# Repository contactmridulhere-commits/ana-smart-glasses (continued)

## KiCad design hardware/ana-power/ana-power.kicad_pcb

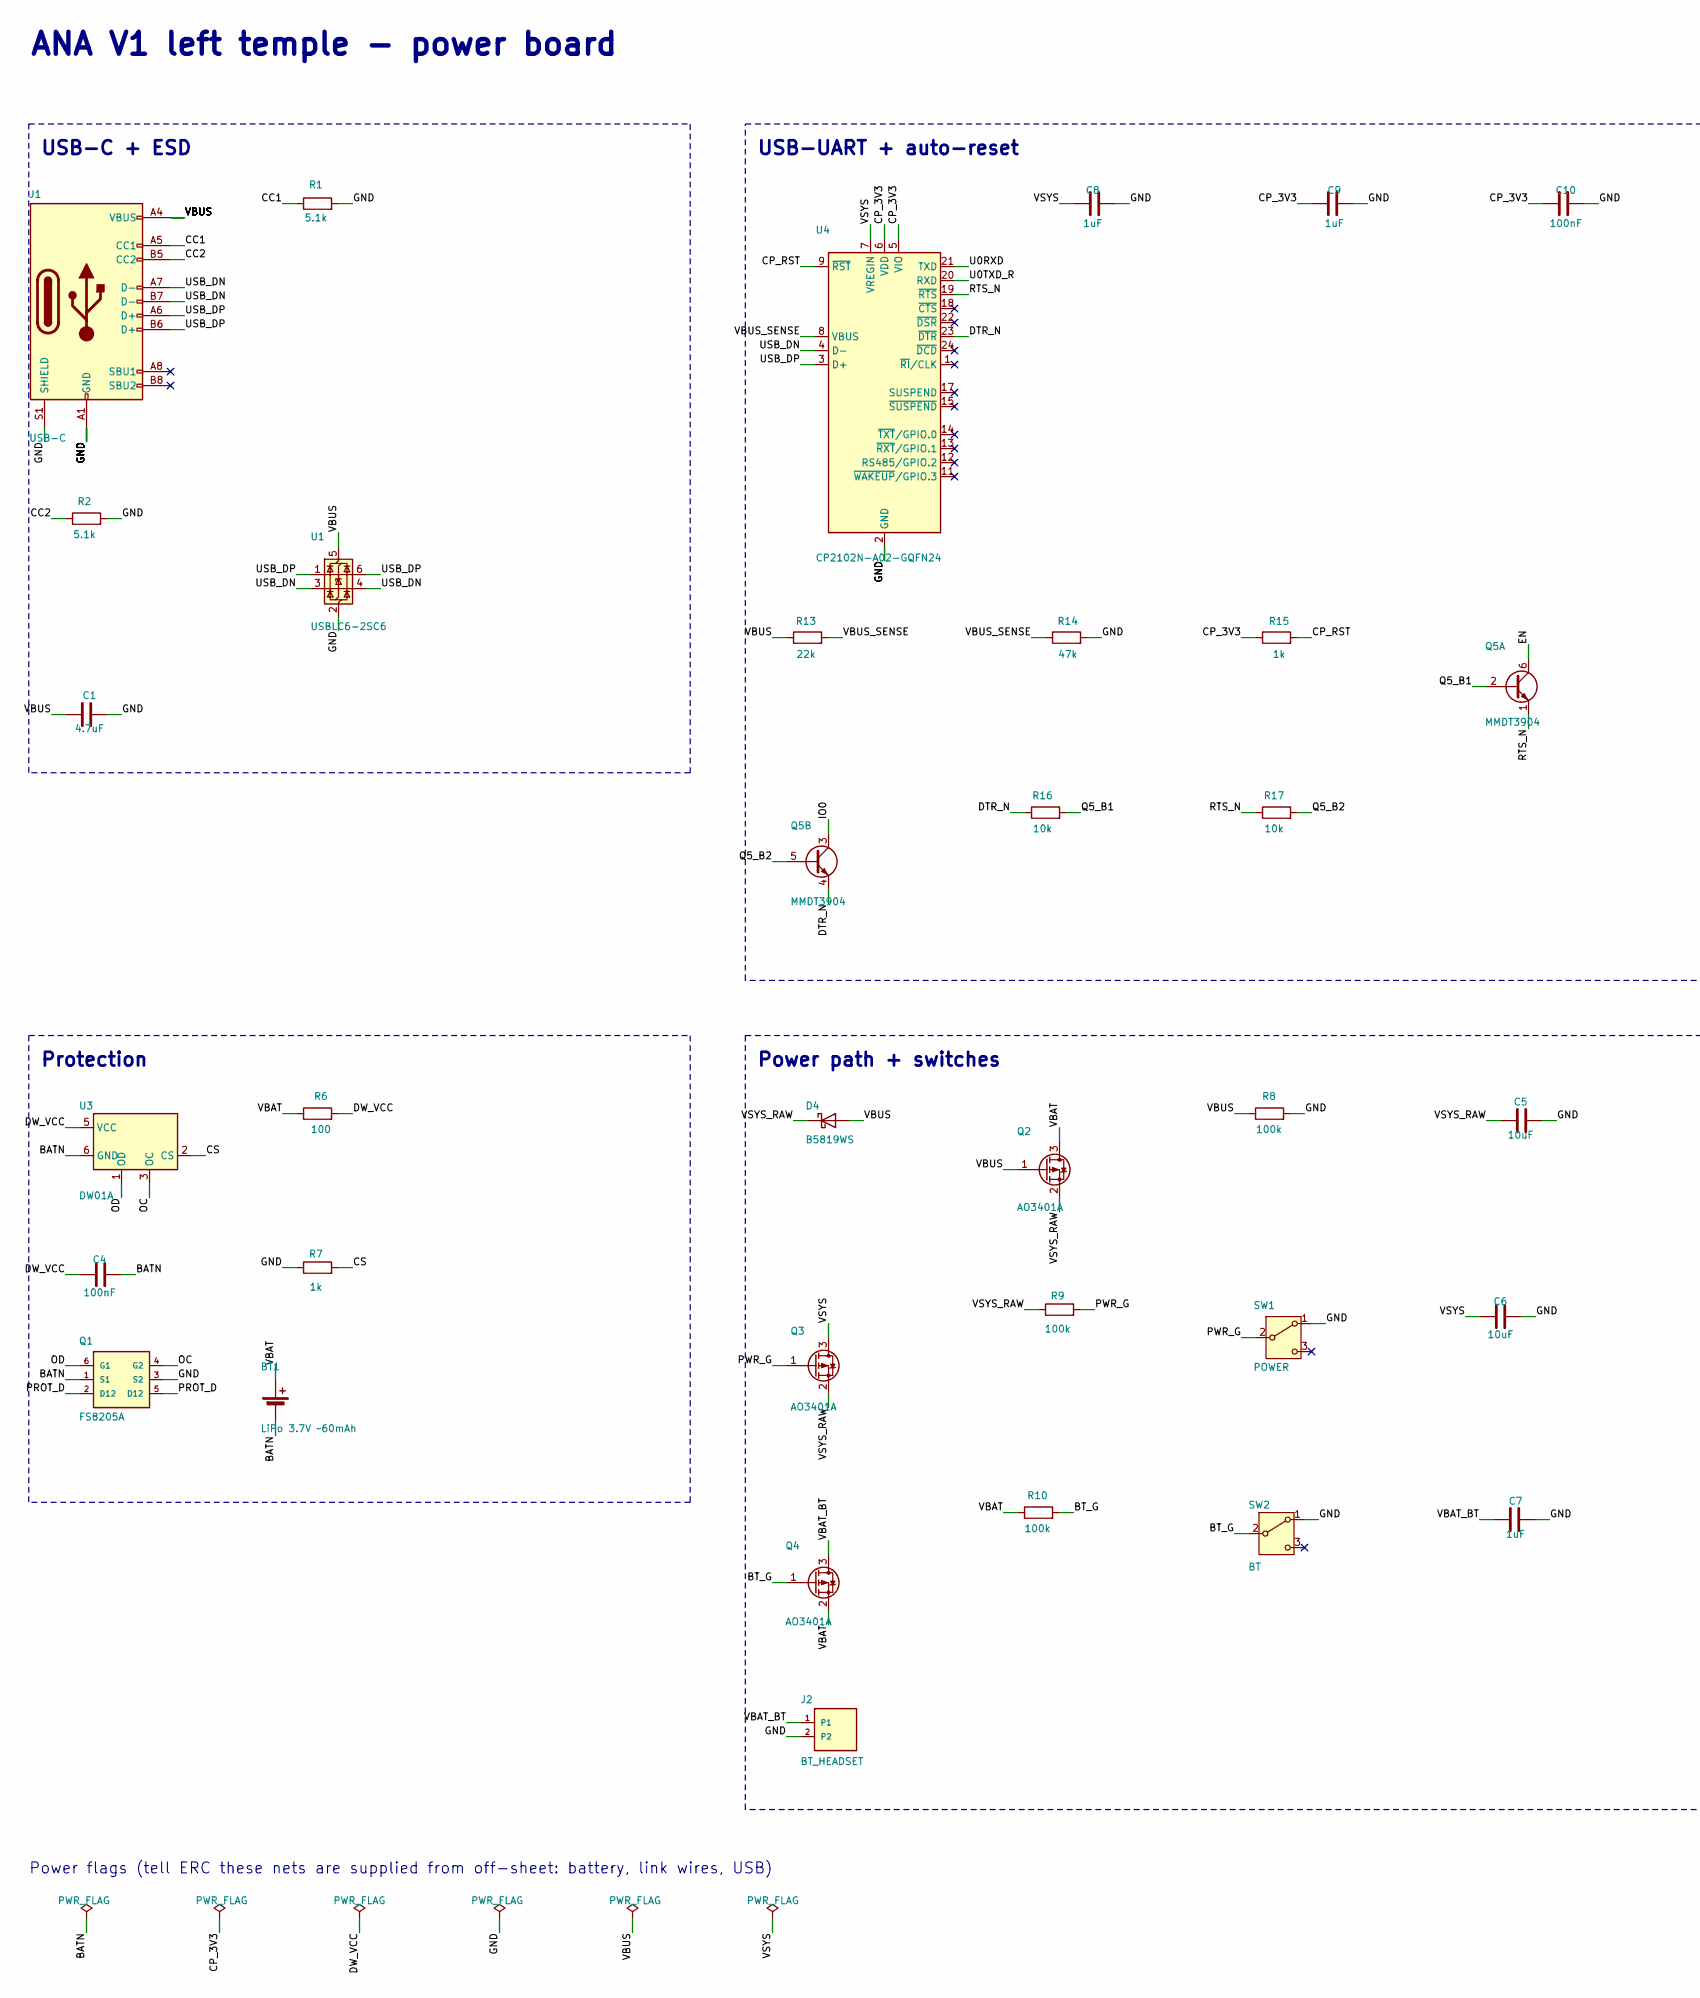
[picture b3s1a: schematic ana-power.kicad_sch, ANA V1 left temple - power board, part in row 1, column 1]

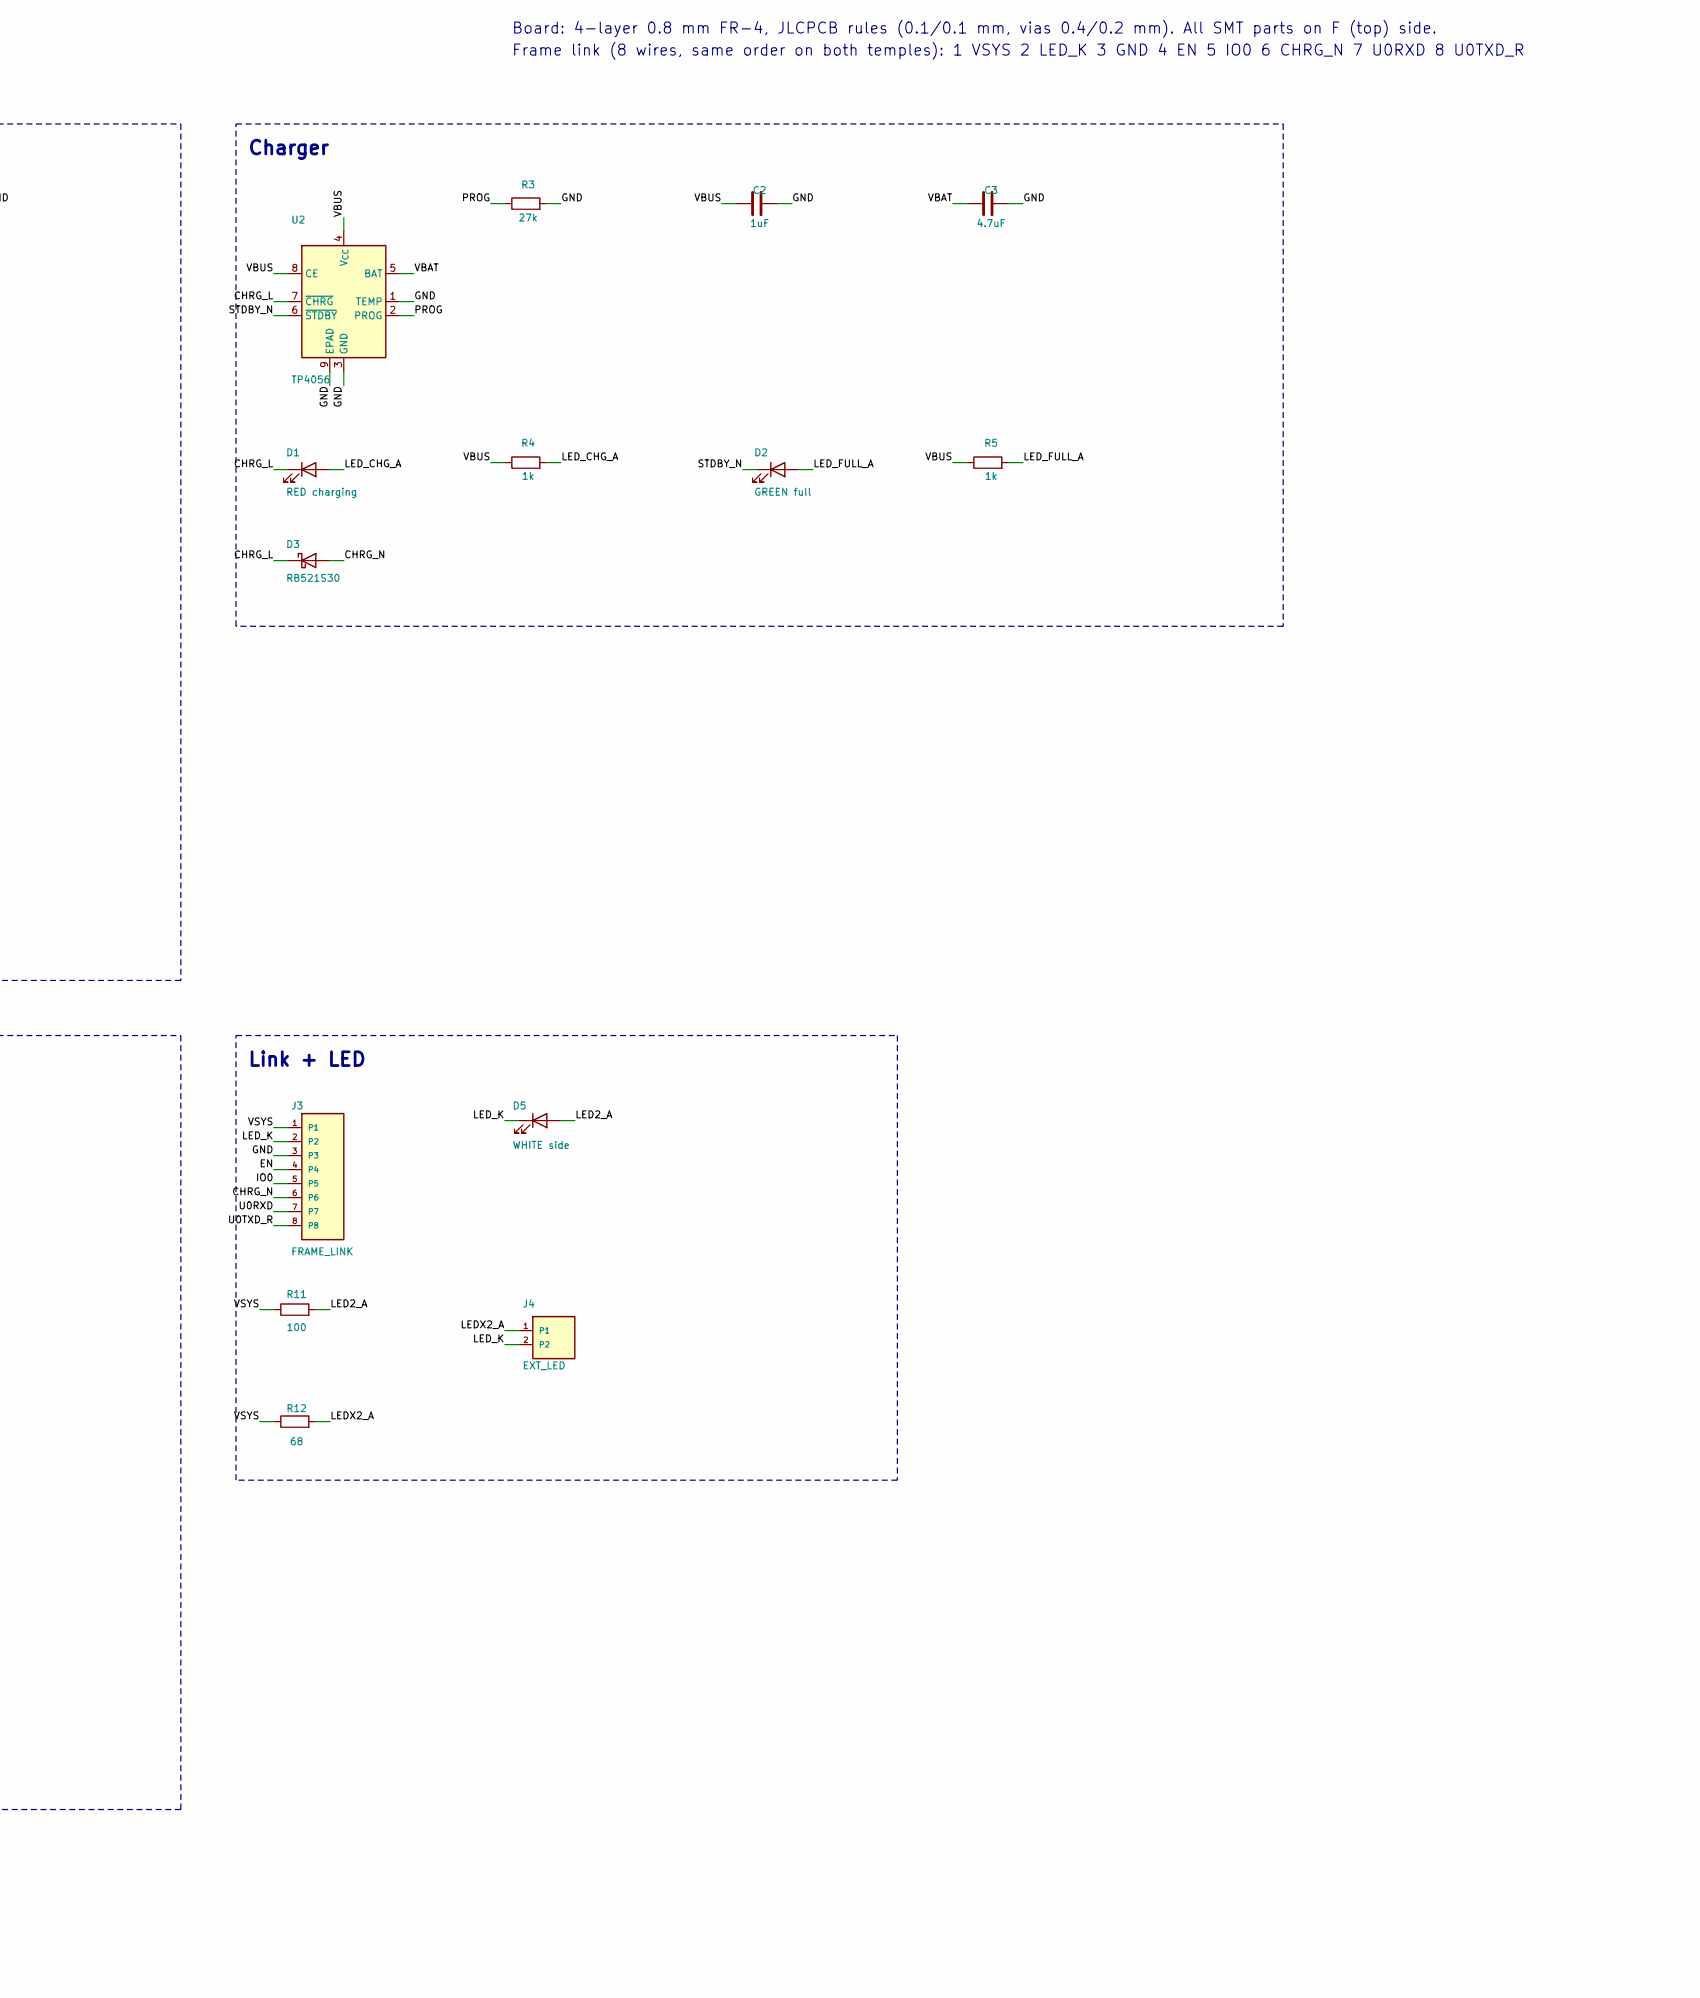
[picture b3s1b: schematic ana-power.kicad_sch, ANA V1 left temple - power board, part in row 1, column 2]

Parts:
BT1: LiPo 3.7V ~60mAh; BatteryPads_2x2.5mm
C1, C3: 4.7uF; C_0402_1005Metric; LCSC C469468
C2, C7, C8, C9: 1uF; C_0402_1005Metric; LCSC C52923
C4, C10: 100nF; C_0402_1005Metric; LCSC C1525
C5, C6: 10uF; C_0603_1608Metric; LCSC C380317
D1: RED charging; LED_0402_1005Metric; MPN NCD0402R1; LCSC C130719
D2: GREEN full; LED_0402_1005Metric; MPN NCD0402G1; LCSC C130723
D3: RB521S30; D_SOD-523; MPN RB521S30T1G; LCSC C145179
D4: B5819WS; D_SOD-323; MPN B5819WS; LCSC C64886
D5: WHITE side; LED_SideView_1.6x0.75mm_YLED0602; MPN YLED0602WSIDE; LCSC C46635136
J1: USB-C; USB_C_Receptacle_HRO_TYPE-C-31-M-12; MPN TYPE-C-31-M-12; LCSC C165948
J2: BT_HEADSET; WirePads_1x02_P1.50mm
J3: FRAME_LINK; WirePads_1x08_P1.50mm
J4: EXT_LED; WirePads_1x02_P1.50mm
Q1: FS8205A; SOT-23-6; MPN FS8205A; LCSC C908265
Q2, Q3, Q4: AO3401A; SOT-23; MPN AO3401A; LCSC C15127
Q5: MMDT3904; SOT-363_SC-70-6; MPN MMDT3904-7-F; LCSC C83572
R1, R2: 5.1k; R_0402_1005Metric; LCSC C25905
R3: 27k; R_0402_1005Metric; LCSC C25771
R4, R5, R7, R15: 1k; R_0402_1005Metric; LCSC C11702
R6, R11: 100; R_0402_1005Metric; LCSC C25076
R8, R9, R10: 100k; R_0402_1005Metric; LCSC C25741
R12: 68; R_0402_1005Metric; LCSC C25131
R13: 22k; R_0402_1005Metric; LCSC C25768
R14: 47k; R_0402_1005Metric; LCSC C25792
R16, R17: 10k; R_0402_1005Metric; LCSC C25744
SW1: POWER; SW_SPDT_Shouhan_MSK12C02; MPN MSK12C02; LCSC C431540
SW2: BT; SW_SPDT_Shouhan_MSK12C02; MPN MSK12C02; LCSC C431540
U1: USBLC6-2SC6; SOT-23-6; MPN USBLC6-2SC6; LCSC C7519
U2: TP4056; HSOP-8-1EP_3.9x4.9mm_P1.27mm_EP2.41x3.1mm; MPN TP4056-42-ESOP8; LCSC C16581
U3: DW01A; SOT-23-6; MPN DW01A; LCSC C351410
U4: CP2102N-A02-GQFN24; QFN-24-1EP_4x4mm_P0.5mm_EP2.6x2.6mm_ThermalVias_NoBottomPad; MPN CP2102N-A02-GQFN24R; LCSC C969151

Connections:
/BATN: BT1.2 (-), C4.2, Q1.1 (S1), U3.6 (GND)
/BT_G: Q4.1 (G), R10.2, SW2.2 (B)
/CC1: J1.A5 (CC1), R1.1
/CC2: J1.B5 (CC2), R2.1
/CHRG_L: D1.1 (K), D3.1 (K), U2.7 (~CHRG)
/CHRG_N: D3.2 (A), J3.6
/CP_3V3: C9.1, C10.1, R15.1, U4.5 (VIO), U4.6 (VDD)
/CP_RST: R15.2, U4.9 (~RST)
/CS: R7.2, U3.2 (CS)
/DTR_N: Q5.4 (E2), R16.1, U4.23 (~DTR)
/DW_VCC: C4.1, R6.2, U3.5 (VCC)
/EN: J3.4, Q5.6 (C1)
/GND: C1.2, C2.2, C3.2, C5.2, C6.2, C7.2, C8.2, C9.2, C10.2, J1.A1 (GND), J1.A12 (GND), J1.B1 (GND), J1.B12 (GND), J1.S1 (SHIELD), J2.2, J3.3, Q1.3 (S2), R1.2, R2.2, R3.2, R7.1, R8.2, R14.2, SW1.1 (A), SW2.1 (A), U1.2 (GND), U2.1 (TEMP), U2.3 (GND), U2.9 (EPAD), U4.2 (GND), U4.25 (GND)
/IO0: J3.5, Q5.3 (C2)
/LED2_A: D5.2 (A), R11.2
/LEDX2_A: J4.1, R12.2
/LED_CHG_A: D1.2 (A), R4.2
/LED_FULL_A: D2.2 (A), R5.2
/LED_K: D5.1 (K), J3.2, J4.2
/OC: Q1.4 (G2), U3.3 (OC)
/OD: Q1.6 (G1), U3.1 (OD)
/PROG: R3.1, U2.2 (PROG)
/PROT_D: Q1.2 (D12), Q1.5 (D12)
/PWR_G: Q3.1 (G), R9.2, SW1.2 (B)
/Q5_B1: Q5.2 (B1), R16.2
/Q5_B2: Q5.5 (B2), R17.2
/RTS_N: Q5.1 (E1), R17.1, U4.19 (~RTS)
/STDBY_N: D2.1 (K), U2.6 (~STDBY)
/U0RXD: J3.7, U4.21 (TXD)
/U0TXD_R: J3.8, U4.20 (RXD)
/USB_DN: J1.A7 (D-), J1.B7 (D-), U1.3 (I/O2), U1.4 (I/O2), U4.4 (D-)
/USB_DP: J1.A6 (D+), J1.B6 (D+), U1.1 (I/O1), U1.6 (I/O1), U4.3 (D+)
/VBAT: BT1.1 (+), C3.1, Q2.3 (D), Q4.2 (S), R6.1, R10.1, U2.5 (BAT)
/VBAT_BT: C7.1, J2.1, Q4.3 (D)
/VBUS: C1.1, C2.1, D4.2 (A), J1.A4 (VBUS), J1.A9 (VBUS), J1.B4 (VBUS), J1.B9 (VBUS), Q2.1 (G), R4.1, R5.1, R8.1, R13.1, U1.5 (VBUS), U2.4 (V_{CC}), U2.8 (CE)
/VBUS_SENSE: R13.2, R14.1, U4.8 (VBUS)
/VSYS: C6.1, C8.1, J3.1, Q3.3 (D), R11.1, R12.1, U4.7 (VREGIN)
/VSYS_RAW: C5.1, D4.1 (K), Q2.2 (S), Q3.2 (S), R9.1

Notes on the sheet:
ANA V1 left temple - power board
Board: 4-layer 0.8 mm FR-4, JLCPCB rules (0.1/0.1 mm, vias 0.4/0.2 mm). All SMT parts on F (top) side.
Frame link (8 wires, same order on both temples): 1 VSYS 2 LED_K 3 GND 4 EN 5 IO0 6 CHRG_N 7 U0RXD 8 U0TXD_R
USB-C + ESD
USB-UART + auto-reset
Charger
Protection
Power path + switches
Link + LED
Power flags (tell ERC these nets are supplied from off-sheet: battery, link wires, USB)

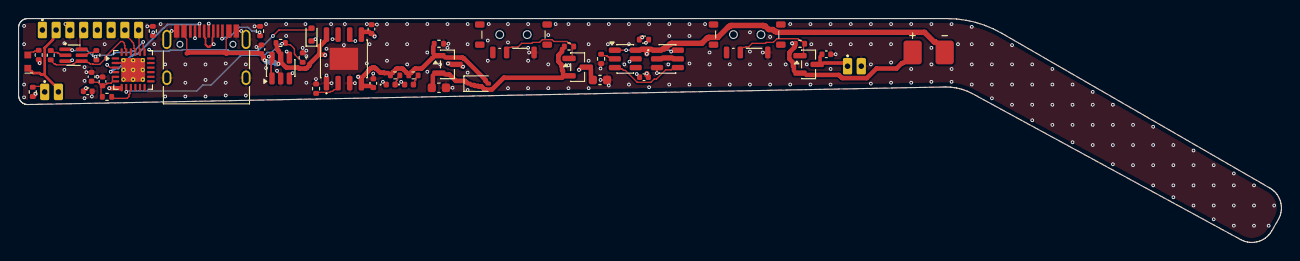
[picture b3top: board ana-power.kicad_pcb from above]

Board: 4 copper layers, 137.8 x 24.4 mm, 48 parts (0 on the bottom side), 38 nets.

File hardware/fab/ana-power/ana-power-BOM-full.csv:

Ref,Value,Footprint,LCSC,MPN,Fitted by,Note
J1,USB-C,Connector_USB:USB_C_Receptacle_HRO_TYPE-C-31-M-12,C165948,TYPE-C-31-M-12,JLCPCB,"charge + firmware upload, bottom edge near hinge"
R1,5.1k,Resistor_SMD:R_0402_1005Metric,C25905,,JLCPCB,UFP Rd
R2,5.1k,Resistor_SMD:R_0402_1005Metric,C25905,,JLCPCB,UFP Rd
U1,USBLC6-2SC6,Package_TO_SOT_SMD:SOT-23-6,C7519,USBLC6-2SC6,JLCPCB,USB ESD
C1,4.7uF,Capacitor_SMD:C_0402_1005Metric,C469468,,JLCPCB,VBUS input (<10 uF per USB spec)
U4,CP2102N-A02-GQFN24,ana:QFN-24-1EP_4x4mm_P0.5mm_EP2.6x2.6mm_ThermalVias_NoBottomPad,C969151,CP2102N-A02-GQFN24R,JLCPCB,"USB-UART; on whenever the glasses are on (own 3.3 V regulator from VSYS), so its pins never back-power the ESP32"
C8,1uF,Capacitor_SMD:C_0402_1005Metric,C52923,,JLCPCB,VREGIN
C9,1uF,Capacitor_SMD:C_0402_1005Metric,C52923,,JLCPCB,VDD (regulator out)
C10,100nF,Capacitor_SMD:C_0402_1005Metric,C1525,,JLCPCB,VDD / VIO
R13,22k,Resistor_SMD:R_0402_1005Metric,C25768,,JLCPCB,VBUS sense divider (self-powered mode)
R14,47k,Resistor_SMD:R_0402_1005Metric,C25792,,JLCPCB,
R15,1k,Resistor_SMD:R_0402_1005Metric,C11702,,JLCPCB,RSTb pull-up (datasheet: 1k)
Q5,MMDT3904,Package_TO_SOT_SMD:SOT-363_SC-70-6,C83572,MMDT3904-7-F,JLCPCB,"ESP32 auto-reset (DTR/RTS), drives EN/IO0 over the link"
R16,10k,Resistor_SMD:R_0402_1005Metric,C25744,,JLCPCB,
R17,10k,Resistor_SMD:R_0402_1005Metric,C25744,,JLCPCB,
U2,TP4056,Package_SO:HSOP-8-1EP_3.9x4.9mm_P1.27mm_EP2.41x3.1mm,C16581,TP4056-42-ESOP8,JLCPCB,"Li-ion linear charger, 4.2 V"
R3,27k,Resistor_SMD:R_0402_1005Metric,C25771,,JLCPCB,Ichg = 1200/27k = 44 mA (0.7C for 60 mAh)
C2,1uF,Capacitor_SMD:C_0402_1005Metric,C52923,,JLCPCB,
C3,4.7uF,Capacitor_SMD:C_0402_1005Metric,C469468,,JLCPCB,BAT pin
D1,RED charging,LED_SMD:LED_0402_1005Metric,C130719,NCD0402R1,JLCPCB,
R4,1k,Resistor_SMD:R_0402_1005Metric,C11702,,JLCPCB,
D2,GREEN full,LED_SMD:LED_0402_1005Metric,C130723,NCD0402G1,JLCPCB,
R5,1k,Resistor_SMD:R_0402_1005Metric,C11702,,JLCPCB,
D3,RB521S30,Diode_SMD:D_SOD-523,C145179,RB521S30T1G,JLCPCB,isolates CHRG to ESP32 (no back-power when off)
U3,DW01A,Package_TO_SOT_SMD:SOT-23-6,C351410,DW01A,JLCPCB,"Li-ion protection (OV 4.3 V, UV 2.4 V, OC)"
R6,100,Resistor_SMD:R_0402_1005Metric,C25076,,JLCPCB,
C4,100nF,Capacitor_SMD:C_0402_1005Metric,C1525,,JLCPCB,
R7,1k,Resistor_SMD:R_0402_1005Metric,C11702,,JLCPCB,CS/VM sense
Q1,FS8205A,Package_TO_SOT_SMD:SOT-23-6,C908265,FS8205A,JLCPCB,"dual N-MOSFET, common drain"
BT1,LiPo 3.7V ~60mAh,ana:BatteryPads_2x2.5mm,,,you (wire/pad),"cell in ear-bend tip, ~3.5 x 7 x 30 mm"
D4,B5819WS,Diode_SMD:D_SOD-323,C64886,B5819WS,JLCPCB,USB -> system when plugged
Q2,AO3401A,Package_TO_SOT_SMD:SOT-23,C15127,AO3401A,JLCPCB,"load sharing: battery -> system, off while USB present"
R8,100k,Resistor_SMD:R_0402_1005Metric,C25741,,JLCPCB,gate pull-down when USB absent
C5,10uF,Capacitor_SMD:C_0603_1608Metric,C380317,,JLCPCB,
Q3,AO3401A,Package_TO_SOT_SMD:SOT-23,C15127,AO3401A,JLCPCB,main power switch FET
R9,100k,Resistor_SMD:R_0402_1005Metric,C25741,,JLCPCB,off by default
SW1,POWER,Button_Switch_SMD:SW_SPDT_Shouhan_MSK12C02,C431540,MSK12C02,JLCPCB,main power slide switch
C6,10uF,Capacitor_SMD:C_0603_1608Metric,C380317,,JLCPCB,
Q4,AO3401A,Package_TO_SOT_SMD:SOT-23,C15127,AO3401A,JLCPCB,BT headset power FET
R10,100k,Resistor_SMD:R_0402_1005Metric,C25741,,JLCPCB,
SW2,BT,Button_Switch_SMD:SW_SPDT_Shouhan_MSK12C02,C431540,MSK12C02,JLCPCB,BT headset slide switch
C7,1uF,Capacitor_SMD:C_0402_1005Metric,C52923,,JLCPCB,
J2,BT_HEADSET,ana:WirePads_1x02_P1.50mm,,,you (wire/pad),to Bluetooth headset module: + / -
J3,FRAME_LINK,ana:WirePads_1x08_P1.50mm,,,you (wire/pad),8-wire link to right temple
D5,WHITE side,ana:LED_SideView_1.6x0.75mm_YLED0602,C46635136,YLED0602WSIDE,JLCPCB,side-emitting white LED at hinge end
R11,100,Resistor_SMD:R_0402_1005Metric,C25076,,JLCPCB,
J4,EXT_LED,ana:WirePads_1x02_P1.50mm,,,you (wire/pad),optional external flashlight LED at the frame corner
R12,68,Resistor_SMD:R_0402_1005Metric,C25131,,JLCPCB,
